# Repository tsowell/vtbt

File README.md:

# Bluetooth to LK201 bridge for DEC video terminals

This repository contains Zephyr RTOS firmware code and KiCad hardware files for
a device which interfaces a DEC VT to a Bluetooth keyboard via an emulated
LK201 interface.

The vtbt board has a socket for an ESP32-C3-DevKitM-1 which provides the
microcontroller and Bluetooth functionality (as well as 3.3V regulation). The
vtbt provides power from the keyboard interface's 12V supply, performs RS-423
level conversion for the serial interface and has the four LEDs and magnetic
buzzer found in a real LK201 because Bluetooth keyboards are unlikely to have
those.

I built this after I spent great effort to obtain a VT420 but then neglected to
use it due to frustrations with the infamous LK401 keyboard. Once I got the
vtbt capable of "self-hosting", I used it with my VT420 to finish developing
the firmware over a serial console. I found that the terminal actually provides
a very enjoyable and relaxing experience with a decent keyboard!

## What works

Everything documented in the VCB02 Video Subsystem Technical manual is
implemented including:

* Beeps, keyclicks, beep and keyclick volumes
* The four LK201 LED indicators
* Per-key-division auto-repeat, up-down, down-only modes
* All mode-setting operations for changing modes and auto-repeat timings

## What doesn't work

I've only tested the vtbt with DEC VT420 terminals.

The key mapping is set up for the VT420's default "<> Key Sends `~" and "`~ Key
Sends ESC" settings. It may need adjustment for other terminals or
configurations.

Similarly, Alt keys, which are disabled by default on the VT420, are not
supported, but support could be added.

Compose keys have not been tested.

## Usage

1. Build and flash the firmware to an ESP32-C3-DevKitM-1 connected over USB.

   From a Zephyr environment:

   ```west flash```

2. Mount the ESP32-C3-DevKitM-1 on the vtbt with the USB port facing the vtbt's
   modular connector and the ESP32-C3 and antenna on the side with the LEDs.

3. Connect the vtbt to a DEC terminal with a rollover-wired 4P4C module cable
   (like a phone handset cable).

4. Turn on the DEC terminal. The vtbt will display the terminal's power-up
   self-test sequence on its four LEDs followed by a beep.

5. Connect to a Bluetooth keyboard.

   The firmware indicates Bluetooth status via the ESP32-C3-DevKitM-1's RGB
   LED.
  
   Blue means it is searching for a Bluetooth keyboard.
  
   Green means it has found a keyboard and is awaiting authorization. To
   authorize, type 123456<Enter> on the keyboard.
  
   Orange means it is connected to a keyboard and processing keyboard events.
  
   The firmware stores bonded devices and automatically reconnects to them.

## Development

The vtbt's modular connector blocks the ESP32-C3-DevKitM-1's USB port, but for
quicker iterations a pair of pin headers as spacers will make it taller.

vtemu.py in this repository can be used as a basic emulation of a DEC terminal
for testing.

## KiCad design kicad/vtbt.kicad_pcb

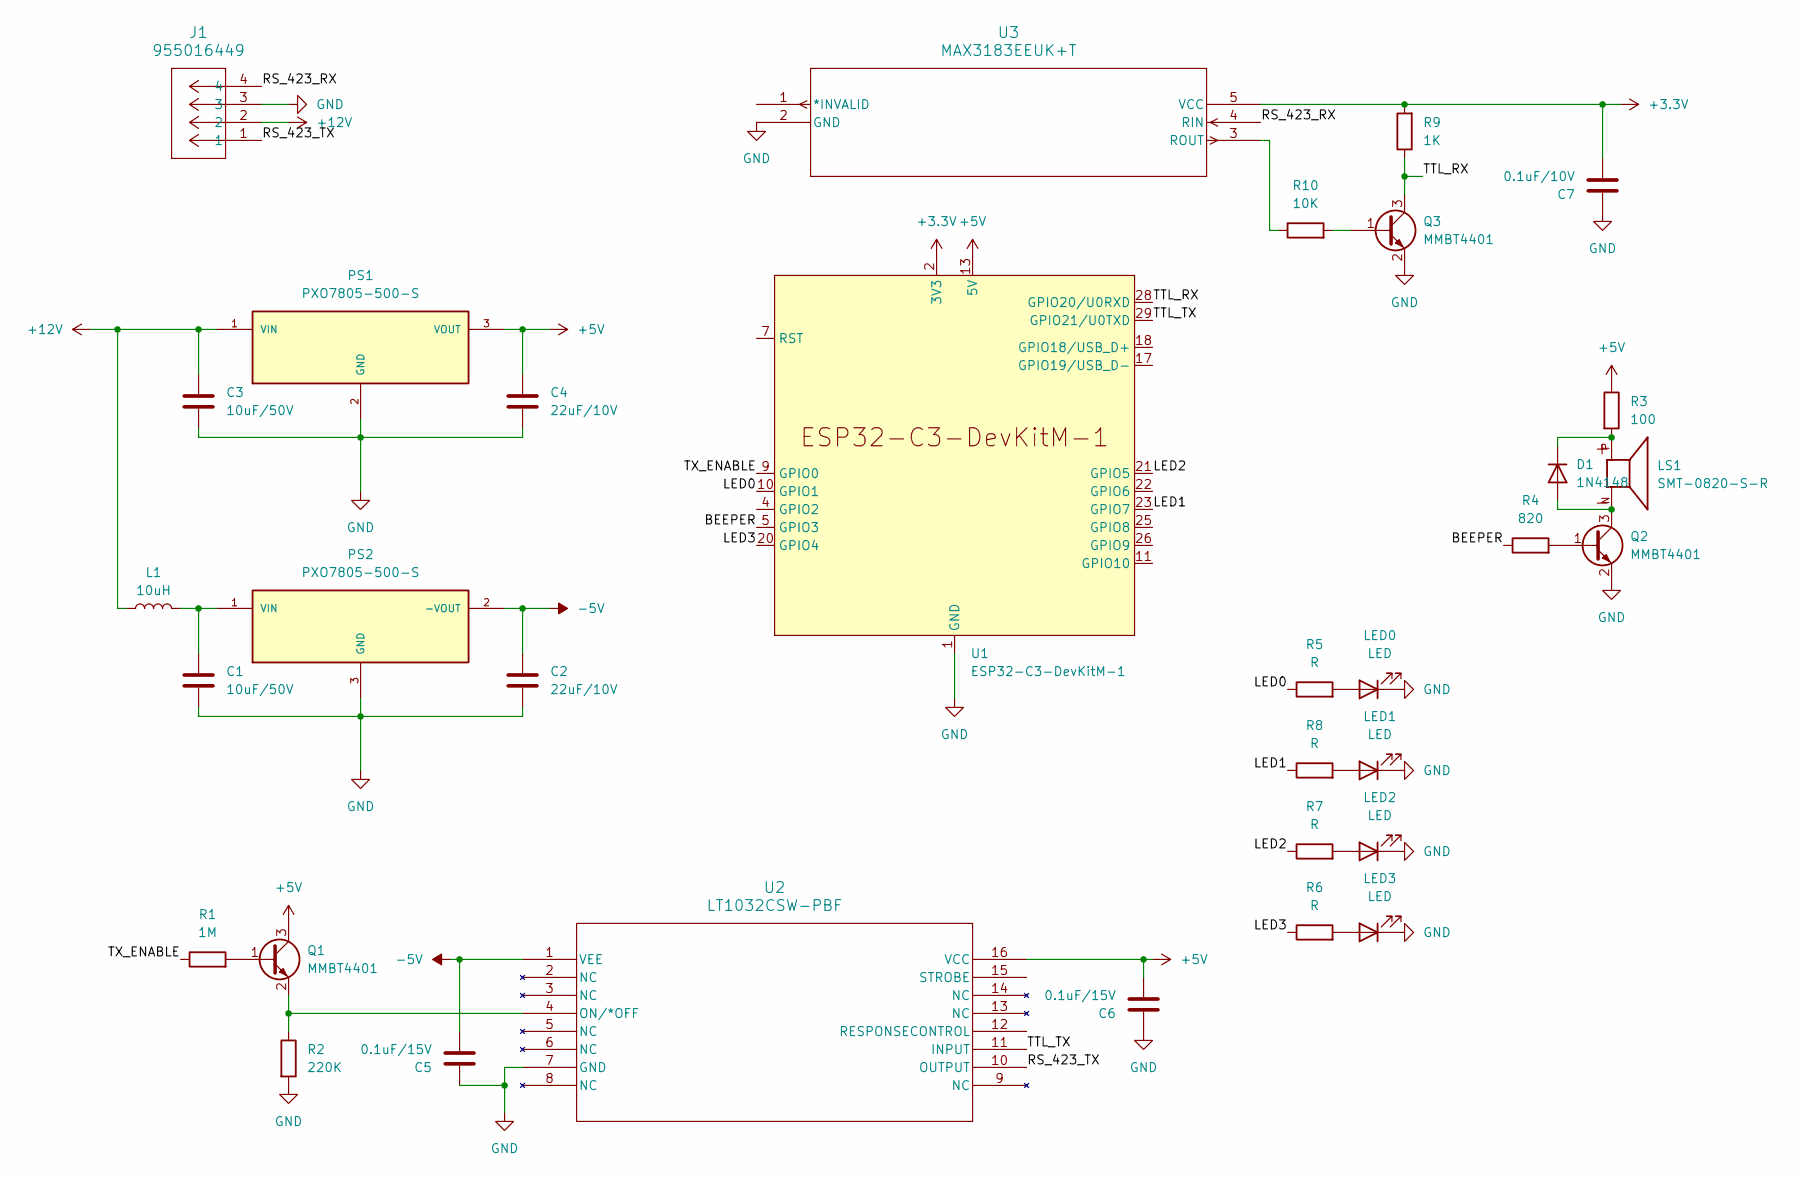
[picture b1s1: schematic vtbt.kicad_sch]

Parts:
C1, C3: 10uF/50V; C_1206_3216Metric_Pad1.33x1.80mm_HandSolder
C2, C4: 22uF/10V; C_0805_2012Metric_Pad1.18x1.45mm_HandSolder
C5, C6: 0.1uF/15V; C_0603_1608Metric
C7: 0.1uF/10V; C_0603_1608Metric
D1: 1N4148; D_SOD-123
J1: 955016449; CONN_95501-6449_MOL
L1: 10uH; L_0603_1608Metric_Pad1.05x0.95mm_HandSolder
LED0, LED1, LED2, LED3: LED; LED_1206_3216Metric_Pad1.42x1.75mm_HandSolder
LS1: SMT-0820-S-R; XDCR_SMT-0820-S-R; PARTREV B
PS1, PS2: PXO7805-500-S; CONV_PXO7805-500-S; PARTREV 08/22/2022
Q1, Q2, Q3: MMBT4401; SOT-23
R1: 1M; R_0603_1608Metric_Pad0.98x0.95mm_HandSolder
R2: 220K; R_0603_1608Metric_Pad0.98x0.95mm_HandSolder
R3: 100; R_0603_1608Metric_Pad0.98x0.95mm_HandSolder
R4: 820; R_0603_1608Metric_Pad0.98x0.95mm_HandSolder
R5, R6, R7, R8: R; R_0603_1608Metric_Pad0.98x0.95mm_HandSolder
R9: 1K; R_0603_1608Metric_Pad0.98x0.95mm_HandSolder
R10: 10K; R_0603_1608Metric_Pad0.98x0.95mm_HandSolder
U1: ESP32-C3-DevKitM-1; ESP32-C3-DevKitM-1_minimal
U2: LT1032CSW-PBF; SOIC-16W_7.5x10.3mm_P1.27mm
U3: MAX3183EEUK+T; SOT-23-5

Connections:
+3.3V: C7.2, R9.2, U1.2 (3V3), U1.3 (3V3), U3.5 (VCC)
+5V: C4.1, C6.2, PS1.3 (VOUT), Q1.3 (C), R3.1, U1.13 (5V), U1.14 (5V), U2.16 (VCC)
+12V: C3.1, J1.2, L1.1, PS1.1 (VIN)
-5V: C2.1, C5.2, PS2.2 (-VOUT), U2.1 (VEE)
/BEEPER: R4.1, U1.5 (GPIO3)
/LED0: R5.1, U1.10 (GPIO1)
/LED1: R8.1, U1.23 (GPIO7)
/LED2: R7.1, U1.21 (GPIO5)
/LED3: R6.1, U1.20 (GPIO4)
/RS_423_RX: J1.4, U3.4 (RIN)
/RS_423_TX: J1.1, U2.10 (OUTPUT)
/TTL_RX: Q3.3 (C), R9.1, U1.28 (GPIO20/U0RXD)
/TTL_TX: U1.29 (GPIO21/U0TXD), U2.11 (INPUT)
/TX_ENABLE: R1.1, U1.9 (GPIO0)
GND: C1.2, C2.2, C3.2, C4.2, C5.1, C6.1, C7.1, J1.3, LED0.1 (K), LED1.1 (K), LED2.1 (K), LED3.1 (K), PS1.2 (GND), PS2.3 (GND), Q2.2 (E), Q3.2 (E), R2.2, U1.1 (GND), U1.6 (GND), U1.8 (GND), U1.12 (GND), U1.15 (GND), U1.16 (GND), U1.19 (GND), U1.24 (GND), U1.27 (GND), U1.30 (GND), U2.7 (GND), U3.2 (GND)
unnamed: D1.2 (A), LS1.N, Q2.3 (C)
unnamed: D1.1 (K), LS1.P, R3.2
unnamed: LED0.2 (A), R5.2
unnamed: LED1.2 (A), R8.2
unnamed: LED2.2 (A), R7.2
unnamed: LED3.2 (A), R6.2
unnamed: C1.1, L1.2, PS2.1 (VIN)
unnamed: Q1.1 (B), R1.2
unnamed: Q1.2 (E), R2.1, U2.4 (ON/*OFF)
unnamed: Q2.1 (B), R4.2
unnamed: Q3.1 (B), R10.2
unnamed: R10.1, U3.3 (ROUT)

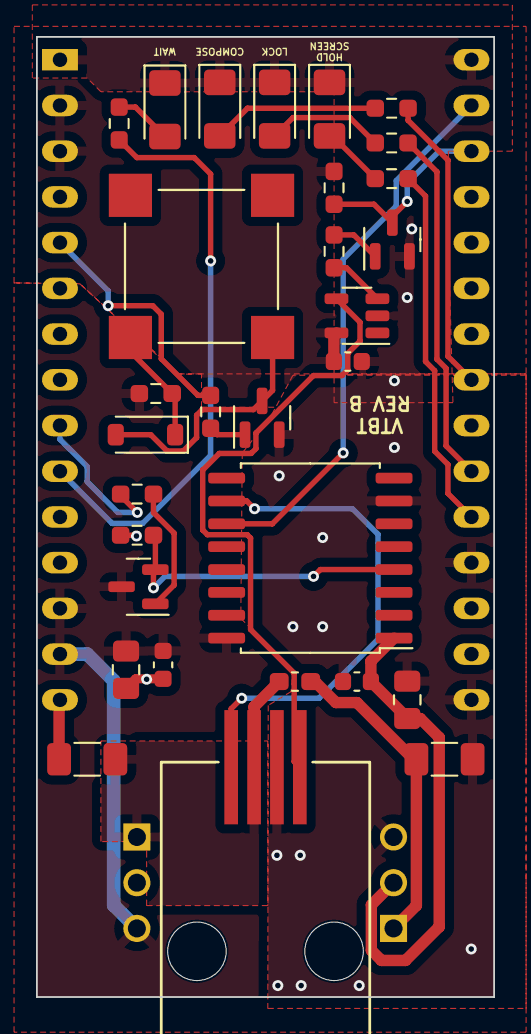
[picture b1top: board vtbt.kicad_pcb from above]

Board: 2 copper layers, 25.4 x 53.3 mm, 33 parts (0 on the bottom side), 27 nets.

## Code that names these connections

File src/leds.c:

#include <zephyr/drivers/gpio.h>
#include <zephyr/logging/log.h>

#include "leds.h"

LOG_MODULE_REGISTER(leds, CONFIG_LOG_DEFAULT_LEVEL);

static const struct gpio_dt_spec leds[NUM_LEDS] = {
	GPIO_DT_SPEC_GET_OR(DT_NODELABEL(led0), gpios, {0}),
	GPIO_DT_SPEC_GET_OR(DT_NODELABEL(led1), gpios, {0}),
	GPIO_DT_SPEC_GET_OR(DT_NODELABEL(led2), gpios, {0}),
	GPIO_DT_SPEC_GET_OR(DT_NODELABEL(led3), gpios, {0}),
};

int
leds_init(void)
{
	int ret;
	for (int i = 0; i < NUM_LEDS; i++) {
		if (!gpio_is_ready_dt(&leds[i])) {
			LOG_ERR("led%d pin GPIO port is not ready.", i);
			return -1;
		}

		ret = gpio_pin_configure_dt(&leds[i], GPIO_OUTPUT_INACTIVE);
		if (ret != 0) {
			LOG_ERR("Configuring led%d GPIO pin failed: %d",
			        i, ret);
			return -1;
		}
	}

	return 0;
}

void
leds_on(int which)
{
	gpio_pin_set_dt(&leds[which], 1);
}

void
leds_off(int which)
{
	gpio_pin_set_dt(&leds[which], 0);
}

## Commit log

2024-02-29 Only load settings when enabled
2024-03-01 Look for boot services
2024-04-28 Add license
2024-04-28 Implement reinstate defaults command
2024-04-28 Keyclick every key down and metronome
2024-04-28 Support Change All Auto Repeat to Down Only
2024-04-28 Inhibit auto repeat, and global enable/disable
2024-04-28 Request keyboard ID
2024-04-28 Read serial messages
2024-04-28 Make division/buffer defaults constant
2024-04-28 HID keys up/down
2024-04-28 Iterate down keys in reverse without temp buffer
2024-04-28 Order functions like VCB02
2024-04-28 ACK reinstate defaults
2024-04-28 Add ARG_UNUSED
2024-04-28 Fix incorrect constant usage
2024-04-28 Fix swapped , and ' keycodes
2024-04-28 Set default volumes
2024-04-28 Remove unused key array
2024-04-28 Use safe dlist macros only when removing
2024-04-28 Use on/off API for LEDs for consistency
2024-04-28 4800 baud
2024-04-28 Initial auto-repeat support
2024-04-28 Test mode
2024-04-28 Fix #define case in leds.h
2024-04-28 Fix misnamed hid_to_lk201_map permanently
2024-04-28 Initial Down/Up key support
2024-04-28 Reorder peripheral command categories like VCB02
2024-04-28 Use int-driven UART, msgqs for keyboard, timer
2024-04-28 Save Bluetooth pairings
2024-04-28 Use default auto-repeat buffer if not specified
2024-04-28 Split into modules
2024-04-28 Handle mode changes
2024-04-28 Add images to README
2024-04-28 Disable saving devices
2024-04-28 Send input error on unrecognized command
2024-04-28 LEDs for pairing status
2024-04-28 LEDs, working on beeper
2024-04-28 Refactor keyboard, metronome handlers into modules
2024-04-28 Add KiCad project
2024-04-28 Refactor flow control into module
2024-04-28 Code reformatting and documentation
2024-04-28 Flow control
2024-04-28 Remap `~ to <> and Esc to `~
    This produces the correct corresponding keycodes with the default VT420
    settings which translate <> to `~ and `~ to Esc.
2024-04-28 Use final LED GPIOs
2024-04-28 Working on serial, refactoring
2024-04-28 Clean up formatting
    bluetooth.c was inherited from Zephyr sample code and needed some
    cleanup for consistency.
2024-04-28 Add vtemu.py for testing
2024-04-28 Refactor command handling
2024-04-28 Set LED to amber for already-bonded devices
2024-04-28 Remove UART mutex
2024-04-28 Add Kconfig
2024-04-28 Add attribution
2024-04-28 Beeper and proof-of-concept key events
2024-04-28 Set board for Zephyr
2024-04-28 Remove old lk201_ prefix in keyboard module
2024-04-28 Remove extra ACKs, add startup responses
    These were discovered through analyzing a real LK201.
2024-04-28 Disable ctrl keyclick by default
2024-04-28 Comment on TX semaphore use
2024-11-18 Reroute for rollover-wired modular cable
    Phone handset cables are commonly available and use rollover-wiring.
